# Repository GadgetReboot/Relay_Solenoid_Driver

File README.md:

# Relay_Solenoid_Driver
32 Channel Relay/Solenoid Driver using MCP23017 and ULN2803 with I2C Control

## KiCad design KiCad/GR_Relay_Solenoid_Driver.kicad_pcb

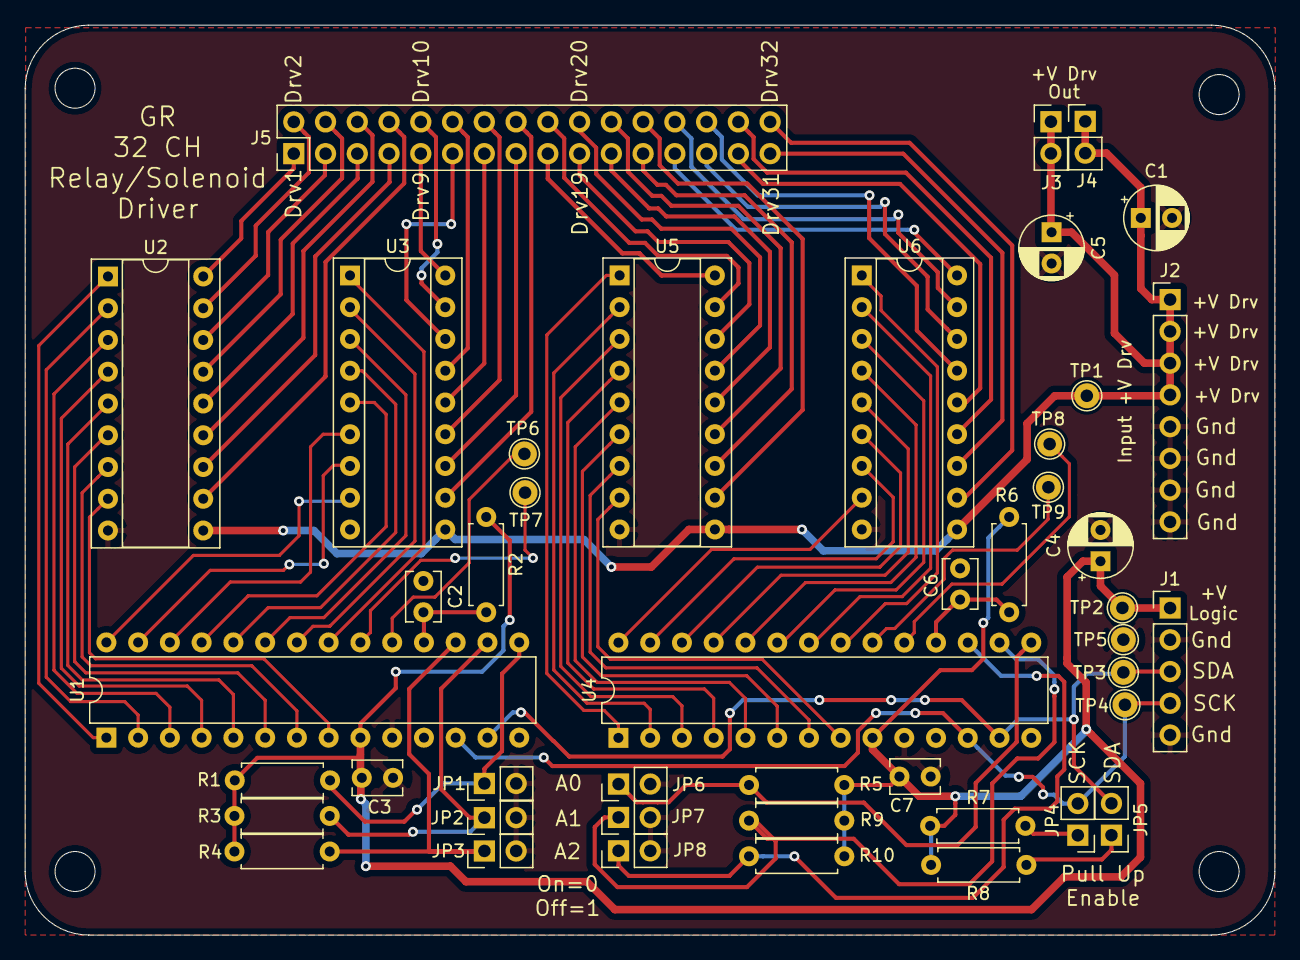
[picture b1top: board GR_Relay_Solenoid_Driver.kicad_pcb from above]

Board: 2 copper layers, 99.9 x 72.8 mm, 49 parts (0 on the bottom side), 83 nets.

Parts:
C1, C4, C5: 10uF; CP_Radial_D5.0mm_P2.50mm
C2, C3, C6, C7: 100nF; C_Disc_D3.8mm_W2.6mm_P2.50mm
J1: Conn_01x05; PinHeader_1x05_P2.54mm_Vertical
J2: Conn_01x08; PinHeader_1x08_P2.54mm_Vertical
J3, J4: Conn_01x02; PinHeader_1x02_P2.54mm_Vertical
J5: Conn_02x16_Odd_Even; PinHeader_2x16_P2.54mm_Vertical
JP1, JP2, JP3, JP4, JP5, JP6, JP7, JP8: Conn_01x02; PinHeader_1x02_P2.54mm_Vertical
MH1, MH2, MH3, MH4: MountingHole; MountingHole_3.2mm_M3
R1, R2, R3, R4, R5, R6, R7, R8, R9, R10: 10K; R_Axial_DIN0207_L6.3mm_D2.5mm_P7.62mm_Horizontal
TP1, TP2, TP3, TP4, TP5, TP6, TP7, TP8, TP9: TestPoint_Alt; TestPoint_THTPad_D2.0mm_Drill1.0mm
U1, U4: MCP23017_SP; DIP-28_W7.62mm
U2, U3, U5, U6: ULN2803; DIP-18_W7.62mm_Socket

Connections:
/Driver 1-16/A0: JP1.1, R1.2, U1.15
/Driver 1-16/A1: JP2.1, R3.2, U1.16
/Driver 1-16/A2: JP3.1, R4.2, U1.17
/Driver 1-16/Out1: U1.1, U2.1
/Driver 1-16/Out2: U1.2, U2.2
/Driver 1-16/Out3: U1.3, U2.3
/Driver 1-16/Out4: U1.4, U2.4
/Driver 1-16/Out5: U1.5, U2.5
/Driver 1-16/Out6: U1.6, U2.6
/Driver 1-16/Out7: U1.7, U2.7
/Driver 1-16/Out8: U1.8, U2.8
/Driver 1-16/Out9: U1.21, U3.1
/Driver 1-16/Out10: U1.22, U3.2
/Driver 1-16/Out11: U1.23, U3.3
/Driver 1-16/Out12: U1.24, U3.4
/Driver 1-16/Out13: U1.25, U3.5
/Driver 1-16/Out14: U1.26, U3.6
/Driver 1-16/Out15: U1.27, U3.7
/Driver 1-16/Out16: U1.28, U3.8
/Driver 17-32/A0: JP6.1, R5.2, U4.15
/Driver 17-32/A1: JP7.1, R9.2, U4.16
/Driver 17-32/A2: JP8.1, R10.2, U4.17
/Driver 17-32/Out1: U4.1, U5.1
/Driver 17-32/Out2: U4.2, U5.2
/Driver 17-32/Out3: U4.3, U5.3
/Driver 17-32/Out4: U4.4, U5.4
/Driver 17-32/Out5: U4.5, U5.5
/Driver 17-32/Out6: U4.6, U5.6
/Driver 17-32/Out7: U4.7, U5.7
/Driver 17-32/Out8: U4.8, U5.8
/Driver 17-32/Out9: U4.21, U6.1
/Driver 17-32/Out10: U4.22, U6.2
/Driver 17-32/Out11: U4.23, U6.3
/Driver 17-32/Out12: U4.24, U6.4
/Driver 17-32/Out13: U4.25, U6.5
/Driver 17-32/Out14: U4.26, U6.6
/Driver 17-32/Out15: U4.27, U6.7
/Driver 17-32/Out16: U4.28, U6.8
/Drv1: J5.1, U2.18
/Drv2: J5.2, U2.17
/Drv3: J5.3, U2.16
/Drv4: J5.4, U2.15
/Drv5: J5.5, U2.14
/Drv6: J5.6, U2.13
/Drv7: J5.7, U2.12
/Drv8: J5.8, U2.11
/Drv9: J5.9, U3.18
/Drv10: J5.10, U3.17
/Drv11: J5.11, U3.16
/Drv12: J5.12, U3.15
/Drv13: J5.13, U3.14
/Drv14: J5.14, U3.13
/Drv15: J5.15, U3.12
/Drv16: J5.16, U3.11
/Drv17: J5.17, U5.18
/Drv18: J5.18, U5.17
/Drv19: J5.19, U5.16
/Drv20: J5.20, U5.15
/Drv21: J5.21, U5.14
/Drv22: J5.22, U5.13
/Drv23: J5.23, U5.12
/Drv24: J5.24, U5.11
/Drv25: J5.25, U6.18
/Drv26: J5.26, U6.17
/Drv27: J5.27, U6.16
/Drv28: J5.28, U6.15
/Drv29: J5.29, U6.14
/Drv30: J5.30, U6.13
/Drv31: J5.31, U6.12
/Drv32: J5.32, U6.11
/SCK: J1.4, JP4.2, TP4.1, U1.12, U4.12
/SDA: J1.3, JP5.2, TP3.1, U1.13, U4.13
GNDREF: C1.2, C2.1, C3.2, C4.2, C5.2, C6.1, C7.2, J1.2, J1.5, J2.5, J2.6, J2.7, J2.8, JP1.2, JP2.2, JP3.2, JP6.2, JP7.2, JP8.2, TP5.1, U1.10, U2.9, U3.9, U4.10, U5.9, U6.9
unnamed: C2.2, R2.2, U1.18
unnamed: C6.2, R6.2, U4.18
unnamed: JP4.1, R7.2
unnamed: JP5.1, R8.2
unnamed: TP6.1, U1.19
unnamed: TP7.1, U1.20
unnamed: TP8.1, U4.19
unnamed: TP9.1, U4.20
VCC: C3.1, C4.1, C7.1, J1.1, R1.1, R2.1, R3.1, R4.1, R5.1, R6.1, R7.1, R8.1, R9.1, R10.1, TP2.1, U1.9, U4.9
Vdrive: C1.1, C5.1, J2.1, J2.2, J2.3, J2.4, J3.1, J3.2, J4.1, J4.2, TP1.1, U2.10, U3.10, U5.10, U6.10
